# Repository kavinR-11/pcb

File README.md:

# PCB Designs

A collection of PCB projects designed using KiCad 9 by Kavin Barath S.

---

## Projects

### 1. Breadboard Power Supply

A multi-rail regulated DC power supply designed for breadboard prototyping.

**Features**
- 3.3V output — LM317L (SOT-89) adjustable linear regulator
- 5V output — LM7805 (TO-220) fixed linear regulator
- 12V pass-through from DC input
- Barrel jack DC input with EG1218 power switch
- LED power indicators per rail
- Screw terminal and pin header outputs

**Schematic & Layout:** `Bread_Board_Power_Supply/`

---

### 2. Tiny Solar Power Supplier

A compact boost-converter PCB for harvesting energy from a small solar panel and stepping it up to a usable output voltage.

**Features**
- AP3015AKTR-G1 boost converter IC
- ASPI-0630LR-100M-T15 100µH power inductor
- SS14 Schottky diode for rectification
- 2N7002 N-channel MOSFET
- 2-pin connectors for solar input and regulated output
- Optimised layout for minimal switching-loop area and low EMI

**Schematic & Layout:** `tiny_solar_power_supplier/`

---

## Tools Used

- [KiCad 9](https://www.kicad.org/) — Schematic capture, PCB layout, DRC

---

## Author

**Kavin Barath S**
- GitHub: [github.com/kavinR-11](https://github.com/kavinR-11)
- LinkedIn: [linkedin.com/in/kavin-barath-s-1958b3324](https://www.linkedin.com/in/kavin-barath-s-1958b3324)
- Email: reach.kavinbarath@gmail.com

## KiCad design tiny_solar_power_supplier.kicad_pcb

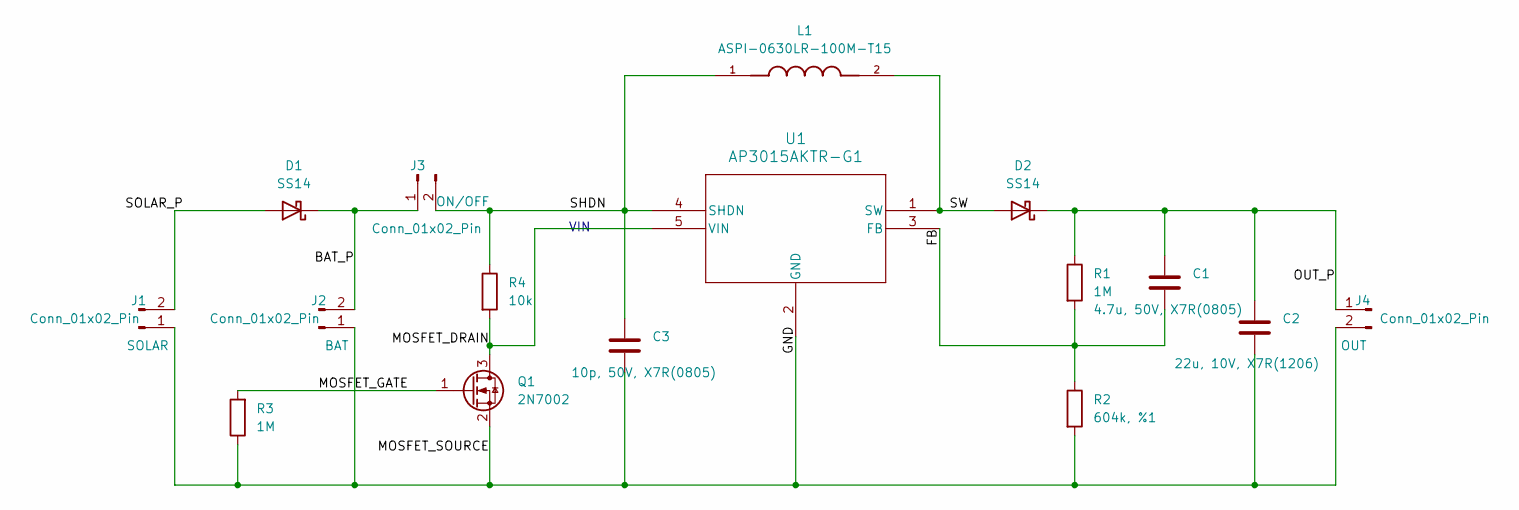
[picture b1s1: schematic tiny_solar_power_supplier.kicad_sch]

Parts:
C1: 4.7u, 50V, X7R(0805); C_0805_2012Metric
C2: 22u, 10V, X7R(1206); C_1206_3216Metric
C3: 10p, 50V, X7R(0805); C_0805_2012Metric
D1, D2: SS14; D_SMA
J1, J2, J4: Conn_01x02_Pin; JST_EH_S2B-EH_1x02_P2.50mm_Horizontal
J3: Conn_01x02_Pin; SW_PUSH_1P1T_6x3.5mm_H5.0_APEM_MJTP1250
L1: ASPI-0630LR-100M-T15; IND_ASPI-0630LR-100M-T15; PARTREV B
Q1: 2N7002; SOT-23
R1, R3: 1M; R_0805_2012Metric
R2: 604k, %1; R_0805_2012Metric
R4: 10k; R_0805_2012Metric
U1: AP3015AKTR-G1; SOT23-5_1P55X2P9_DIO-L

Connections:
/BAT_P: D1.1 (K), J2.2, J3.1
/FB: C1.2, R1.2, R2.1, U1.3 (FB)
/GND: C2.2, C3.2, J1.1, J2.1, J4.2, Q1.2 (S), R2.2, R3.1, U1.2 (GND)
/MOSFET_DRAIN: Q1.3 (D), R4.2, U1.5 (VIN)
/MOSFET_GATE: Q1.1 (G), R3.2
/OUT_P: C1.1, C2.1, D2.1 (K), J4.1, R1.1
/SHDN: C3.1, J3.2, L1.1, R4.1, U1.4 (SHDN)
/SOLAR_P: D1.2 (A), J1.2
/SW: D2.2 (A), L1.2, U1.1 (SW)

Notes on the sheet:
VIN

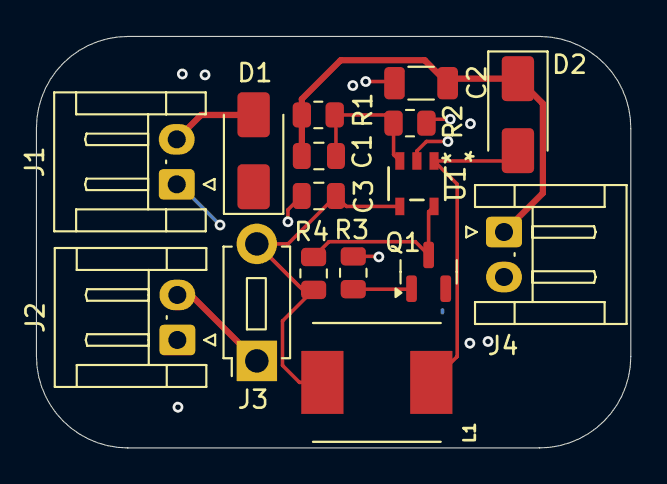
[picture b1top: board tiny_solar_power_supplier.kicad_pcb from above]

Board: 2 copper layers, 33.0 x 22.9 mm, 16 parts (0 on the bottom side), 9 nets.

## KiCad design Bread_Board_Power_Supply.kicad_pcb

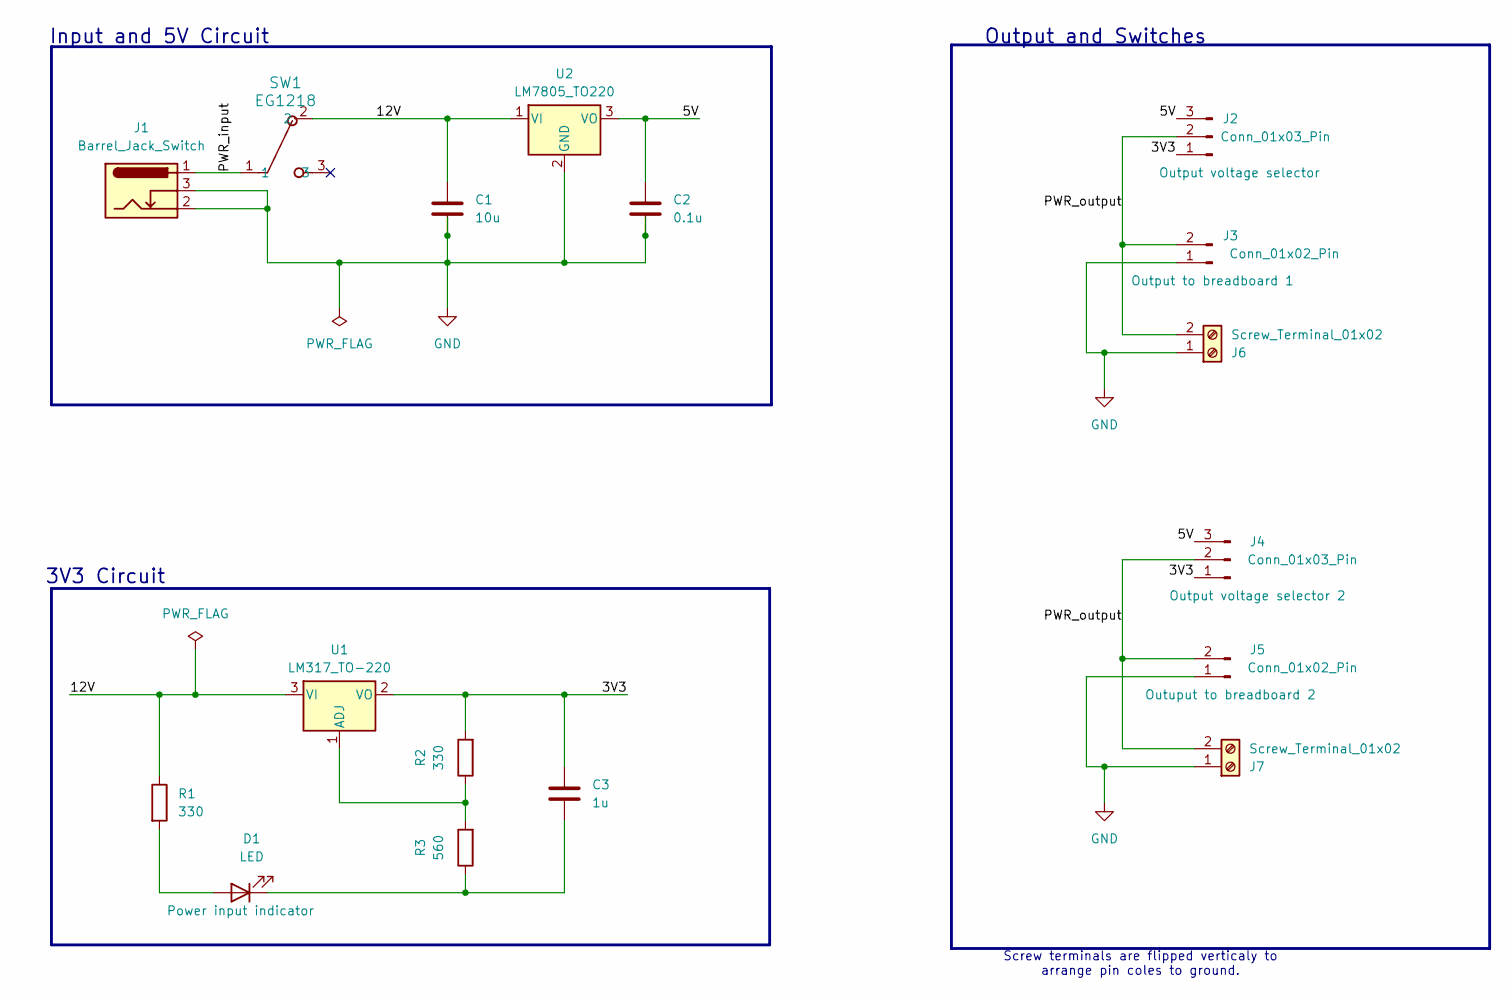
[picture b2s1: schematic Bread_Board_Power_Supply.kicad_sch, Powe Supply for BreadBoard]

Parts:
C1: 10u; C_Disc_D3.0mm_W1.6mm_P2.50mm
C2: 0.1u; C_Disc_D3.0mm_W1.6mm_P2.50mm
C3: 1u; C_Disc_D3.0mm_W1.6mm_P2.50mm
D1: LED; TerminalBlock_bornier-2_P5.08mm
J1: Barrel_Jack_Switch; BarrelJack_Horizontal
J2: Conn_01x03_Pin; PinSocket_1x03_P2.54mm_Vertical
J3, J5: Conn_01x02_Pin; PinSocket_1x02_P2.54mm_Vertical
J4: Conn_01x03_Pin; PinHeader_1x03_P2.54mm_Vertical
J6, J7: Screw_Terminal_01x02; TerminalBlock_bornier-2_P5.08mm
R1, R2: 330; R_Axial_DIN0204_L3.6mm_D1.6mm_P7.62mm_Horizontal
R3: 560; R_Axial_DIN0204_L3.6mm_D1.6mm_P7.62mm_Horizontal
SW1: EG1218; Switch_Slide_11.6x4mm_EG1218
U1: LM317_TO-220; TO-220-3_Vertical
U2: LM7805_TO220; TO-220-3_Vertical

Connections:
/3V3: C3.2, J2.1, J4.1, R2.2, U1.2 (VO)
/5V: C2.1, J2.3, J4.3, U2.3 (VO)
/12V: C1.1, R1.1, SW1.2, U1.3 (VI), U2.1 (VI)
/PWR_input: J1.1, SW1.1
/PWR_output: J2.2, J3.2, J4.2, J5.2, J6.2, J7.2
GND: C1.2, C2.2, J1.2, J1.3, J3.1, J5.1, J6.1, J7.1, U2.2 (GND)
unnamed: D1.2 (A), R1.2
unnamed: C3.1, D1.1 (K), R3.1
unnamed: R2.1, R3.2, U1.1 (ADJ)

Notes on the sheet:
Output and Switches
Screw terminals are flipped verticaly to arrange pin coles to ground.
Input and 5V Circuit
3V3 Circuit

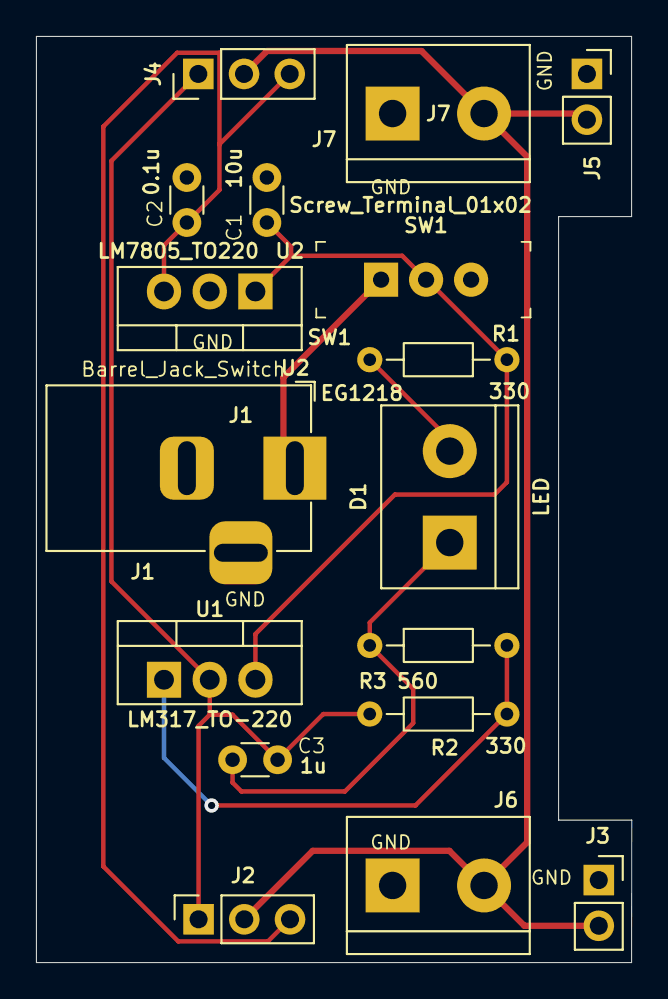
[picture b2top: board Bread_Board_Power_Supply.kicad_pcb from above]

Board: 2 copper layers, 33.1 x 51.5 mm, 17 parts (0 on the bottom side), 9 nets.
